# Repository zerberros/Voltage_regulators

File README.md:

# Voltage_regulators
Collection of switching voltage regulators

## BUCK LMR33630

[BUCK LMR33630](https://www.ti.com/lit/ds/symlink/lmr33630.pdf)

* Input voltage range: 3.8V to 36V
* Output voltage: Configured at 3.3V
* Output current: Up to 3A

[schematic](BUCK_LMR33630/documentation/BUCK_LMR33630.pdf)

## BUCK LM2576

* ONLY Schematics
* Replaced by LMR33630

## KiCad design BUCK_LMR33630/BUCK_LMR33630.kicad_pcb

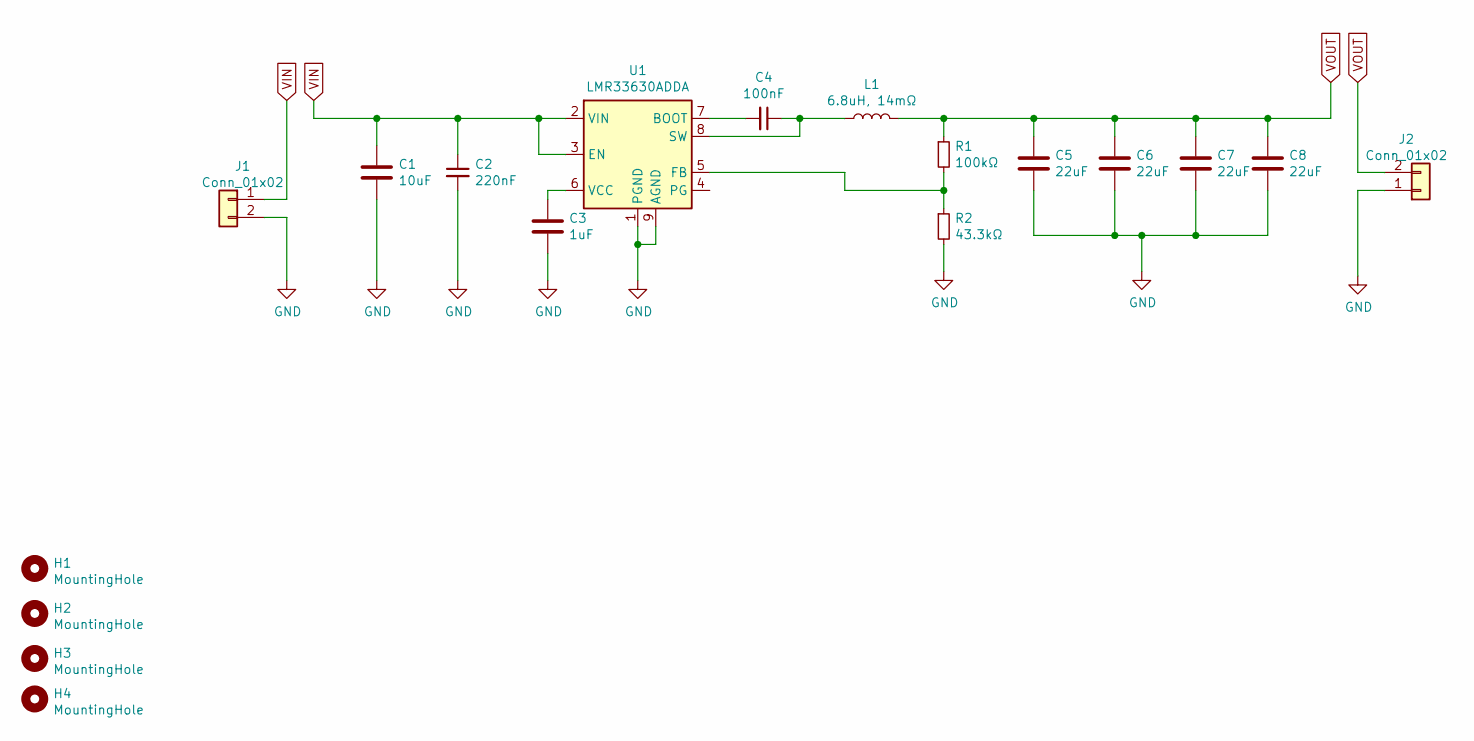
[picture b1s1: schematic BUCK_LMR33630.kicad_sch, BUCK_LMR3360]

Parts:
C1: 10uF; C_1206_3216Metric_Pad1.33x1.80mm_HandSolder
C2: 220nF; C_1206_3216Metric_Pad1.33x1.80mm_HandSolder
C3: 1uF; C_1206_3216Metric_Pad1.33x1.80mm_HandSolder
C4: 100nF; C_1206_3216Metric_Pad1.33x1.80mm_HandSolder
C5, C6, C7, C8: 22uF; C_1206_3216Metric_Pad1.33x1.80mm_HandSolder
H1, H2, H3, H4: MountingHole; MountingHole_3.2mm_M3
J1, J2: Conn_01x02; TerminalBlock_Phoenix_MKDS-1,5-2-5.08_1x02_P5.08mm_Horizont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; MPN 1985865
L1: 6.8uH, 14mΩ; L_Bourns-SRU1028_10.0x10.0mm; MPN SRU1048-6R8Y
R1: 100kΩ; R_1206_3216Metric_Pad1.30x1.75mm_HandSolder
R2: 43.3kΩ; R_1206_3216Metric_Pad1.30x1.75mm_HandSolder
U1: LMR33630ADDA; Texas_HSOP-8-1EP_3.9x4.9mm_P1.27mm_ThermalVias; MPN LMR33630ADDA

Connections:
GND: C1.2, C2.2, C3.2, C5.2, C6.2, C7.2, C8.2, J1.2, J2.1, R2.2, U1.1 (PGND), U1.9 (AGND)
unnamed: C3.1, U1.6 (VCC)
unnamed: C4.1, L1.1, U1.8 (SW)
unnamed: C4.2, U1.7 (BOOT)
unnamed: R1.2, R2.1, U1.5 (FB)
VIN: C1.1, C2.1, J1.1, U1.2 (VIN), U1.3 (EN)
VOUT: C5.1, C6.1, C7.1, C8.1, J2.2, L1.2, R1.1

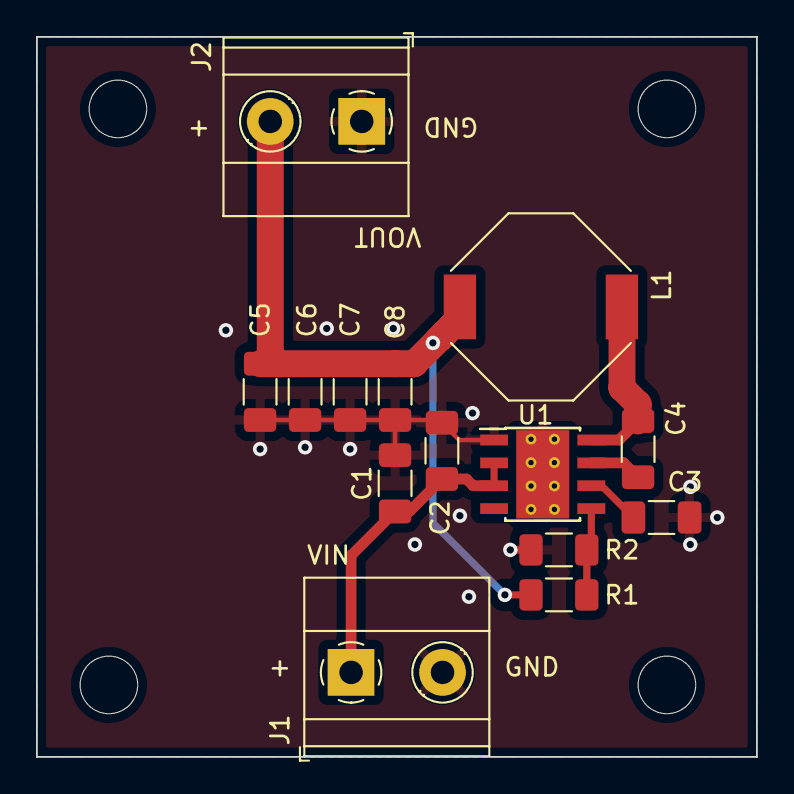
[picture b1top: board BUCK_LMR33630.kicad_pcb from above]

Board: 2 copper layers, 40.0 x 40.0 mm, 18 parts (0 on the bottom side), 7 nets.

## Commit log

2021-04-10 move repository
2021-04-10 Added another regulator
2021-04-11 Update doc
2021-04-11 Fix namefolder

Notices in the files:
BUCK_LMR33630/BUCK_LMR33630.kicad_pcb:
CERN-OHL-P v2
